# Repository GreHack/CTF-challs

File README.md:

Here are some of the challenges (including sources) of the
[GreHack](https://grehack.fr) CTF:
 * [GreHack'15](/2015)
 * [GreHack'16](/2016)
 * [GreHack'17](/2017)
 * [GreHack'18](/2018)
 * [GreHack'19](/2019)
 * [GreHack'22](/2022)
 * [GreHack'23](/2023)

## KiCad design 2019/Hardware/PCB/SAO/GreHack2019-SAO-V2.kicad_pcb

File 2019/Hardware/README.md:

# Hardware Challenges

This folder contains all the source code of the 8 hardware challenge played during the CTF.

## Continue to play at home with the badge you get during the CTF :

If you want to continu playing, it's possible without spoiler.          
In this case, just open subfolder [CTF_at_home](CTF_at_home/) and you'll find the 8 subjects.             
The only difference is that I'm not here to do the firmware reloading, so my scripts are included in the folder. During the CTF you had to figure it out by yourself.           
Feel free to reach me on Twitter if you have questions or want some hints  --> @PagetPhil       

## The sources code :

Everything was done with the official Arduino's IDE for the firmwares and a Linux for the file encrypting or files generator.          
If you want to recompil the various firmwares, you must add all the [libraries](Sources/Libraries/) included in your arduino IDE.         

## Photos :

Just for fun, a few pictures taken during the project. Enjoy!                

## PCB (coming soon !) :

Will contains sources files for KiCAD, the GERBER files and the BOM.

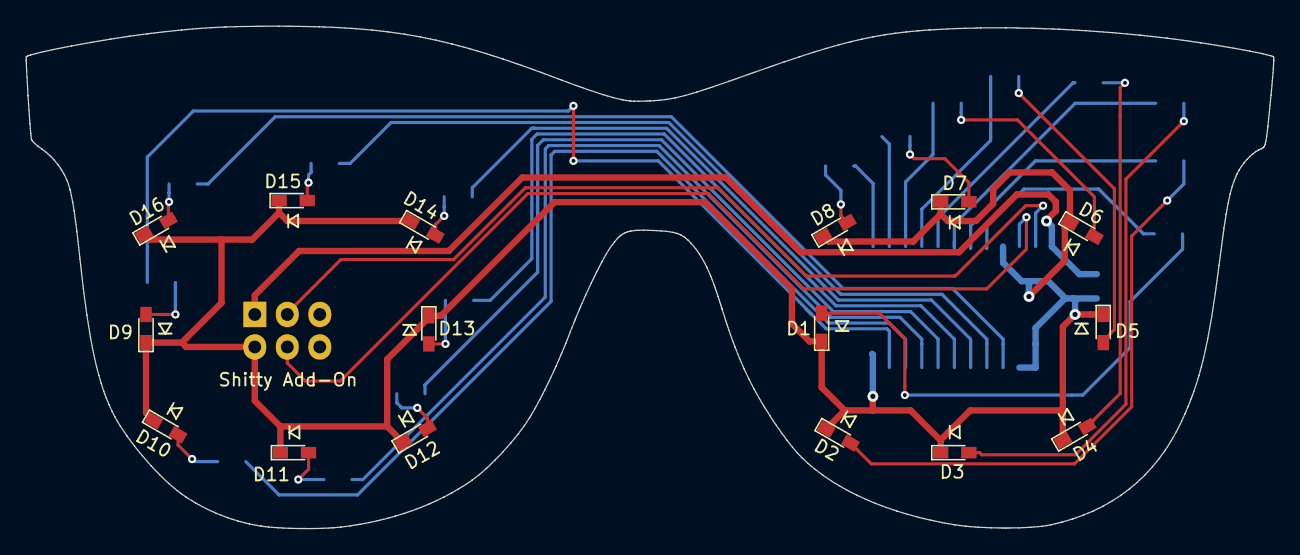
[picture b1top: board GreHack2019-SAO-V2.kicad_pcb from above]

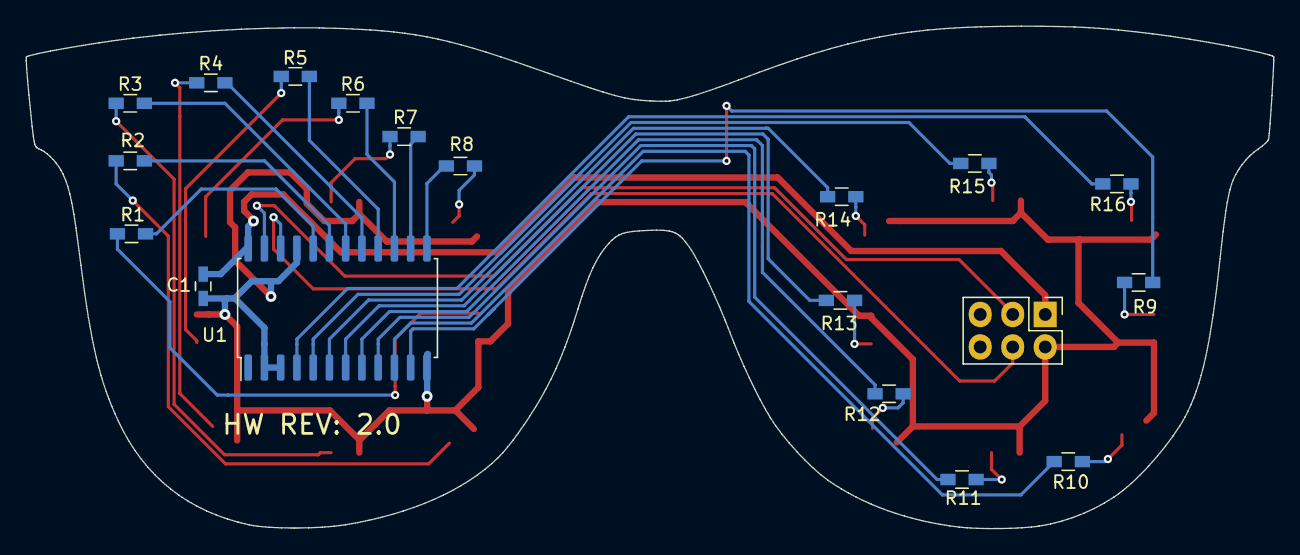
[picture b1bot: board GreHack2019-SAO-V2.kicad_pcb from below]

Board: 2 copper layers, 97.5 x 39.3 mm, 35 parts (19 on the bottom side), 36 nets.

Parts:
C1: 100n; C_0603_HandSoldering
D1, D2, D3, D4, D5, D6, D7, D8, D9, D10, D11, D12, D13, D14, D15, D16: LED; LED_0603_HandSoldering
J1: Shitty Add-On; Pin_Header_Straight_2x03_Pitch2.54mm
R1, R2, R3, R4, R5, R6, R7, R8, R9, R10, R11, R12, R13, R14, R15, R16: R158; R_0603_HandSoldering
U1: PCA9535; SOIC-24W_7.5x15.4mm_P1.27mm

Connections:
+3V3: C1.1, J1.1, U1.24
GND: C1.2, D1.1, D2.1, D3.1, D4.1, D5.1, D6.1, D7.1, D8.1, D9.1, D10.1, D11.1, D12.1, D13.1, D14.1, D15.1, D16.1, J1.2, U1.2, U1.3, U1.12, U1.21
unnamed: D1.2, R1.1
unnamed: D2.2, R2.1
unnamed: D3.2, R3.1
unnamed: D4.2, R4.1
unnamed: D5.2, R5.1
unnamed: D6.2, R6.1
unnamed: D7.2, R7.1
unnamed: D8.2, R8.1
unnamed: D9.2, R9.1
unnamed: D10.2, R10.1
unnamed: D11.2, R11.1
unnamed: D12.2, R12.1
unnamed: D13.2, R13.1
unnamed: D14.2, R14.1
unnamed: D15.2, R15.1
unnamed: D16.2, R16.1
unnamed: R1.2, U1.20
unnamed: R2.2, U1.19
unnamed: R3.2, U1.18
unnamed: R4.2, U1.17
unnamed: R5.2, U1.16
unnamed: R6.2, U1.15
unnamed: R7.2, U1.14
unnamed: R8.2, U1.13
unnamed: R9.2, U1.11
unnamed: R10.2, U1.10
unnamed: R11.2, U1.9
unnamed: R12.2, U1.8
unnamed: R13.2, U1.7
unnamed: R14.2, U1.6
unnamed: R15.2, U1.5
unnamed: R16.2, U1.4
SCL: J1.4, U1.22
SDA: J1.3, U1.23

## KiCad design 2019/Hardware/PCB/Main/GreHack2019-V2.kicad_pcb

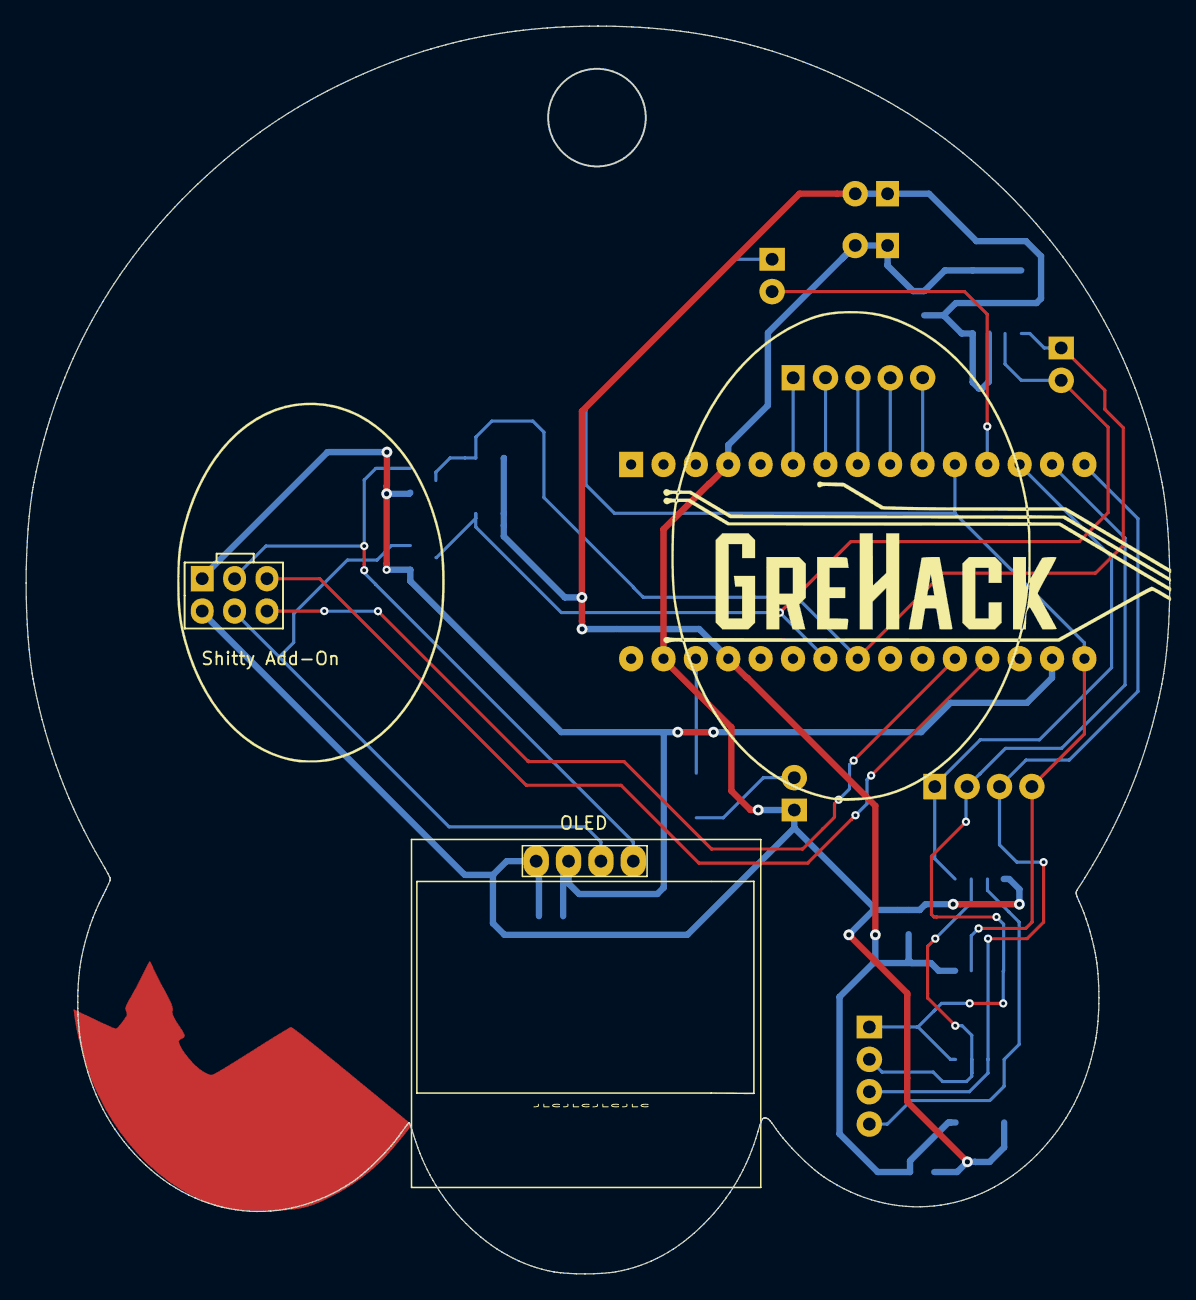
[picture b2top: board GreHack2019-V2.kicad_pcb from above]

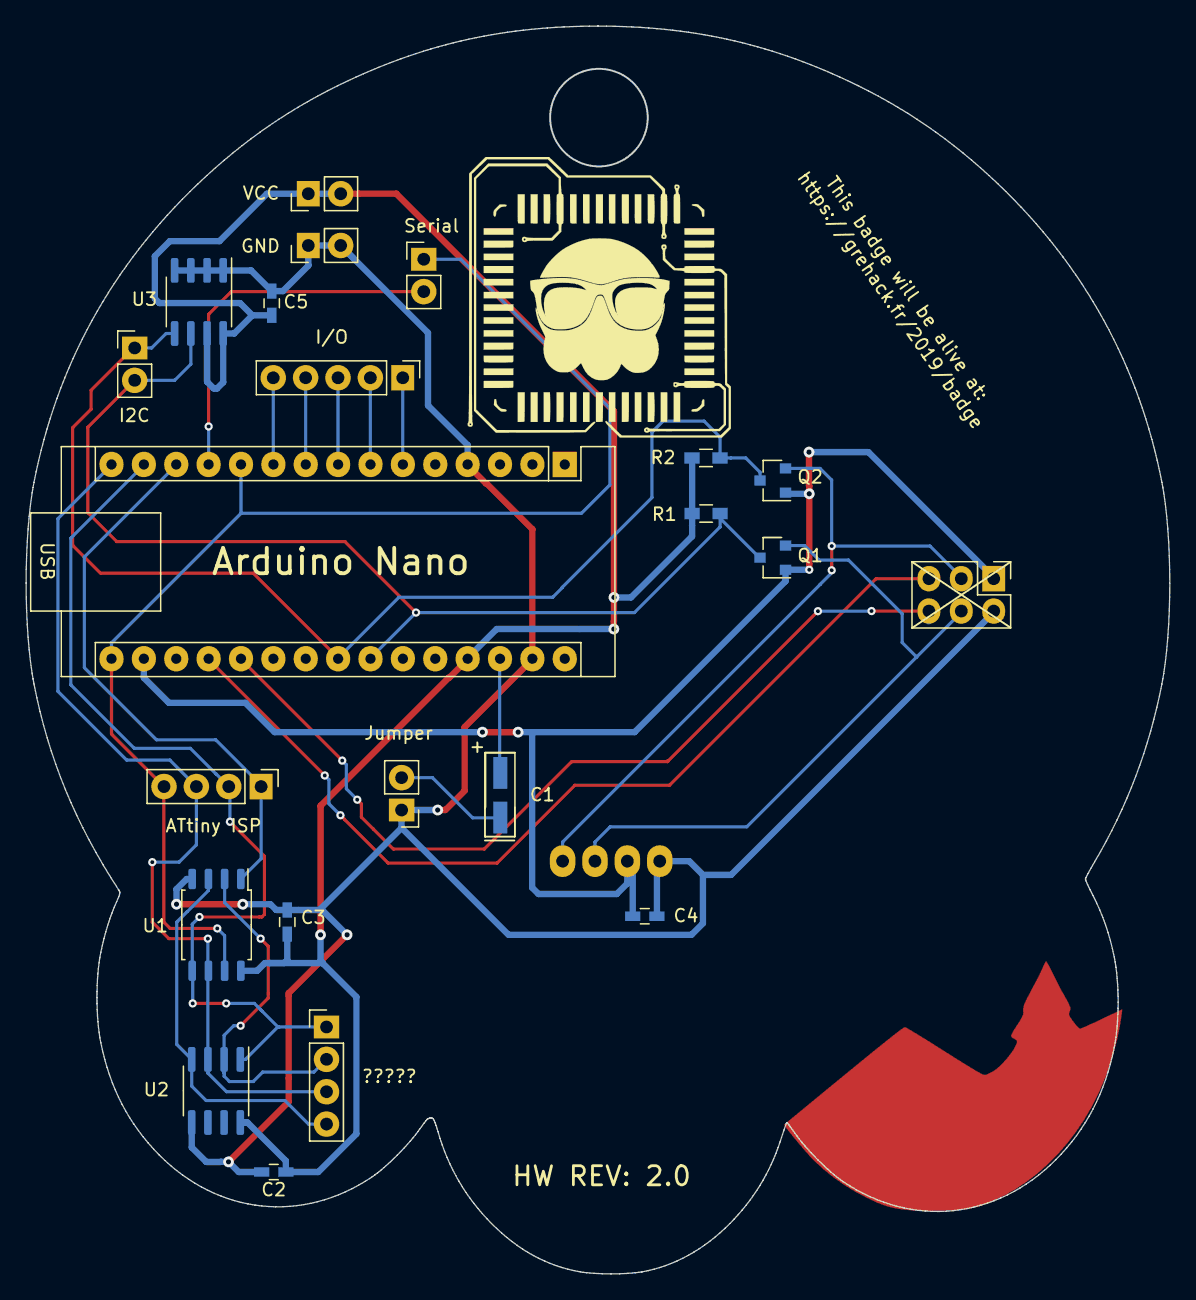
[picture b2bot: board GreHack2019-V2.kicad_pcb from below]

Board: 2 copper layers, 89.7 x 97.8 mm, 23 parts (22 on the bottom side), 23 nets.

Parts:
A1: Arduino Nano; Arduino_Nano
Brd1: SSD1306; 128x64OLED
C1: 10u; CP_Tantalum_Case-R_EIA-2012-12_Hand
C2, C3, C4, C5: 100n; C_0603_HandSoldering
J1: Shitty Add-On; Pin_Header_Straight_2x03_Pitch2.54mm
J2: Microwire bus; Pin_Header_Straight_1x04_Pitch2.54mm
J3: Serial; Pin_Header_Straight_1x02_Pitch2.54mm
J4: ATtiny ISP; Pin_Header_Straight_1x04_Pitch2.54mm
J5: Jumper; Pin_Header_Straight_1x02_Pitch2.54mm
J6: GND; Pin_Header_Straight_1x02_Pitch2.54mm
J7: VCC; Pin_Header_Straight_1x02_Pitch2.54mm
J8: I2C bus; Pin_Header_Straight_1x02_Pitch2.54mm
J9: 5 GPIO; Pin_Header_Straight_1x05_Pitch2.54mm
Q1, Q2: BSS138; SOT-23
R1, R2: 10k; R_0603_HandSoldering
U1: ATtiny85; SOIC-8_5.23x5.23mm_P1.27mm
U2: 93LCxxC; SOIC-8_3.9x4.9mm_P1.27mm
U3: 24LC16; SOIC-8_3.9x4.9mm_P1.27mm

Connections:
+3V3: A1.17, Brd1.2, C4.2, J1.1, Q1.1, Q2.1
+5V: A1.27, C2.1, C3.2, C5.2, J7.1, J7.2, R1.1, R2.1, U1.8, U2.8, U3.7, U3.8
?_1: A1.14, J2.1, J4.2, U1.5, U2.1
?_2: J2.2, U1.2, U2.2
?_3: A1.15, J2.3, J4.3, U1.6, U2.3
?_4: J2.4, U1.3, U2.4
GND: A1.4, A1.29, Brd1.1, C2.2, C3.1, C4.1, C5.1, J1.2, J5.1, J6.1, J6.2, U1.4, U2.5, U3.1, U3.2, U3.3, U3.4
GPIO1: A1.6, J9.1
GPIO2: A1.7, J9.2
GPIO3: A1.8, J9.3
GPIO4: A1.9, J9.4
GPIO5: A1.10, J9.5
ISP_RST: A1.13, J4.1, U1.1
ISP_SCK: A1.11, A1.16, J3.1, J4.4, U1.7
unnamed: A1.12, J3.2
unnamed: A1.23, J8.1, Q2.3, R2.2, U3.5
unnamed: A1.24, J8.2, Q1.3, R1.2, U3.6
unnamed: A1.28, C1.1
unnamed: Brd1.3, J1.4, Q1.2
unnamed: Brd1.4, J1.3, Q2.2
unnamed: C1.2, J5.2
SAO-IO1: A1.19, J1.5
SOA-IO2: A1.20, J1.6

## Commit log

2016-11-22 Add web 50
2016-11-22 Fix Web 50 readme
2016-11-22 Add web 150
2016-11-22 Add web 250
2016-11-22 Add web 400
2016-11-22 Fix READMEs of web 50 and 150
2016-11-22 Add Reverse 250
2016-11-22 Order challenges by points inside folder
2016-11-22 Add steganography 50
2016-11-23 Add stego challs
2016-11-23 title in README.md
2016-11-23 add network100 chall
2016-11-23 f**k README.md
2016-11-23 Add reverse 50 chall
2016-11-23 remove flag.txt
2016-11-23 Add forensic 100 chall
2016-11-23 Add reverse chall 100 150 250 500
2016-11-23 Fix category of Very Well hidden challenge
    Close #1
2016-12-04 add reverse 250_solveme source and crypto 100 pizzas
2017-11-19 GH17: Add Hardware 100
2017-11-19 GH17: Add Reverse 250
2017-11-19 GH17 Hardware 100 respect naming convention
2017-11-19 GH17: Add Web 50
2017-11-19 Fix GH web 50 and RE 250 README
    Newlines should be forced
2017-11-20 Add Reverse challenges from 2015
2017-11-20 Stego100
2017-11-20 Stego100 chall.bmp
2017-11-20 Readme1
2017-11-20 Readme2
2017-11-20 Readme3
2017-11-20 Readme
2017-11-20 Stego200
2017-11-20 GH17: Add Stego100 and Stego200 (#4)
    * Stego100
    * Stego100 chall.bmp
    * Readme1
    * Readme2
    * Readme3
    * Readme
2017-11-20 Added pwn50 and pwn150
2017-11-20 GH17: Add Web 250
2017-11-20 GH17: Add Web 400
2017-11-20 Add Reverse challenges from 2015 (#5)
2017-11-20 Add all reverse challs from 2015
2017-11-20 Add minimal README
2017-11-20 Give the right flag for GH17 Web 400
    I'm tired of myself…
2017-11-20 Fix READMEs GH17 exploit 50 and 150
2017-11-21 Add files via upload
    Add all files
2017-11-22 Add Reverse 400 - Joe
2017-11-22 Add Stego50
2017-11-22 Added exploit 200 and exploit 250
2017-11-22 Fix README format
2017-11-22 Typo
2017-11-23 Correction title stego200
2017-11-23 Add Bounty challenge in the blockchain section
2017-11-23 Add blockchain bounty chall to writeup.md
2017-11-28 Add blockchain challs + organize blockchain/bounty chall
2017-11-28 Add readme for Blockchain/Casino, add Forensic 200
2018-11-19 Update README.md
    docker-compose start gave an error:
    Starting web ... done
    ERROR: No containers to start,
    Let me know if I missed anything.
2018-11-19 Added 2018 logo and "rusty" challenge
2018-11-19 Added "rusty" sources
2018-11-19 Adding Crypto250 sources and solution
2018-11-19 Adding sources and solution for Crypto300
2018-11-19 Adding number of points to directories
2018-11-19 Deleting old directories
2018-11-19 Add GH18 Web 50
2018-11-19 Add license file for GH18 Web 50 challenge
2018-11-19 Fix instructions to launch the web challenges with Docker Compose
    Close #14.
2018-11-19 Add GH18 RE 100
2018-11-20 Add GH18 Web 350
2018-11-20 Adding sources code for Hardware challenges level 1-6
2018-11-23 adding sources,tools and solutions for Reverse 300 - Forgotten Hardware
2018-12-04 Add more reverse challs from 2018 CTF
2019-11-16 Init GH19
2019-11-16 Add GH19 Web 50 YurEvent
2019-11-16 Add GH19 Web 75 Diagnostic tools
2019-11-16 Add GH19 Web 150 ORM Login
2019-11-16 Add GH19 Web 400 Internal Resources (again)
2019-11-18 adding the 8 hardware challenges
2019-11-18 Add GH19 Reverse 100 xordump
2019-11-19 Add GH19 Reverse 350 'TacitApparatus'
2019-11-19 Huge solving speedup for the test program (challenge stays unchanged)
2019-11-19 Adds LPN challs
2019-11-19 Added GH19 Reverse 250 'The Point'
2019-11-19 Better README.md
2019-11-19 Added GH19 Reverse 200 "Dolos' offering"
2019-11-19 Added GH19 Reverse 200 "Dolos' offering" (#22)
2019-11-19 Add ssh challenge
2019-11-19 Cleanup 2019 READMEs and structure
2019-11-20 Add 2019 White-box challenge
2019-11-22 Add 100 - AngryTux chall
2019-11-22 Add Spider Collection chall
2019-11-22 Update exploit.py
    Change name from my variable
2019-11-23 Add 100 - AngryTux chall (#25)
2019-12-03 Bump symfony/http-foundation
    Bumps [symfony/http-foundation](https://github.com/symfony/http-foundation) from 4.1.7 to 4.4.1.
    - [Release notes](https://github.com/symfony/http-foundation/releases)
    - [Changelog](https://github.com/symfony/http-foundation/blob/master/CHANGELOG.md)
    - [Commits](https://github.com/symfony/http-foundation/compare/v4.1.7...v4.4.1)
2020-02-01 Add GH19 blockchain challenges
2022-11-05 Add challs from 2013
2022-11-06 Add reverse prechalls from 2018 'Corrupted Memories'
2022-11-20 Add GH22 Game Over 3 (Hardware 400)
2022-11-20 Add GH22 Yaknet challenges
2022-11-20 Add GH22 Web 150 `FaaS`
2022-11-20 Add GH22 Misc 100 Shitposting
2022-11-20 Add link to the folder containing the code to solve the GH22 FaaS chall
2022-11-20 stuff to publishing
2022-11-22 2022: Add cafebabe chall
2022-11-22 2022: Add Lucky Luks challenge
2022-11-22 Add GH22 XOROT
2022-11-22 Add GH 22 Crypto chall Counting-On-You
2022-11-22 Move the possible solution of Counting-On-You into a spoiler tag
2022-11-23 Add web + misc challenges
2023-08-10 adding PCB files to GreHack 2019 Hardware challenges
2023-11-20 Create folder for GreHack'23
2023-11-20 Add web challenge Guiding You
2023-11-20 Add crypto challenge ECB Landing Pad
2023-11-20 Move Guiding You into web subfolder
2023-11-20 Add OSINT challenge Oink!
2024-05-18 add all 2023 challenges
